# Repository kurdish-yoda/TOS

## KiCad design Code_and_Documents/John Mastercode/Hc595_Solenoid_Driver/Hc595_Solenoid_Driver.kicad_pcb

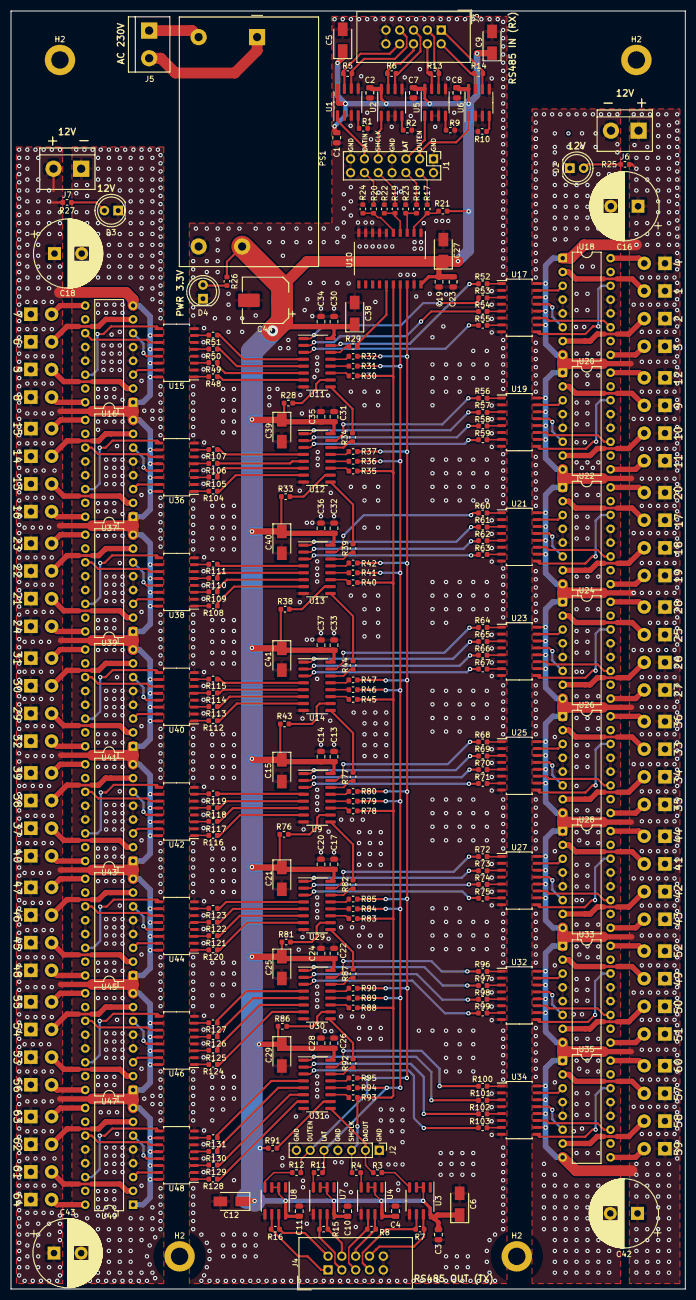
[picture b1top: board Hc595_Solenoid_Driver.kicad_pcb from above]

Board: 2 copper layers, 124.0 x 235.0 mm, 303 parts (0 on the bottom side), 355 nets.

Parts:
C1, C2, C3, C4, C7, C8, C10, C11, C13, C17, C19, C22, C26, C30, C31, C32, C33: 100nF; C_0805_2012Metric_ValInMiddleFABlayer
C5, C6, C9, C12, C15, C21, C25, C27, C29, C38, C39, C40, C41: 4.7uF; D_SMA_SMA_Capacitor
C14, C20, C23, C24, C28, C34, C35, C36, C37: 10nF; C_0805_2012Metric_ValInMiddleFABlayer
C16, C18, C42, C43: 470uF; CP_Radial_D12.5mm_P5.00mm
C44: 470uF; CP_Elec_8x5.4_ModifFABlayer
D2, D3, D4: LD271; LED_D5.0mm_IRGrey
H2, H2#2, H2#3, H2#4: MountingHole_3.2mm_M3_DIN965_Pad_ModifFABlayer
J1: Conn_02x07_Counter_Clockwise; PinHeader_2x07_P2.54mm_Vertical_ModifFABlayer
J2: Conn_01x07; PinHeader_1x07_P2.54mm_Vertical
J3, J4: Conn_02x05_Odd_Even; IDC-Header_2x05_P2.54mm_Vertical_ModifFABlayer
J5, J6, J7: Screw_Terminal_01x02; TerminalBlock_bornier-2_P5.08mm
J8, J9, J10, J11, J12, J13, J14, J15, J16, J17, J18, J19, J20, J21, J22, J23, J24, J25, J26, J27, J28, J29, J30, J31, J32, J33, J34, J35, J36, J37, J38, J39, J40, J41, J42, J43, J44, J45, J46, J47, J48, J49, J50, J51, J52, J53, J54, J55, J56, J57, J58, J59, J60, J61, J62, J63, J64, J65, J66, J67, J68, J69, J70, J71: Conn_01x02; SolderWirePad_1x02_P3.81mm_Drill1.2mm_Diam2.5mm
PS1: IRM-10-3.3; Converter_ACDC_MeanWell_IRM-10-xx_THT
R1, R2, R9, R10: 22k; R_0603_1608Metric_ValInMiddleFABlayer
R3, R4, R11, R12, R17, R18, R19, R20, R29, R30, R31, R32, R34, R35, R36, R37, R39, R40, R41, R42, R44, R45, R46, R47, R77, R78, R79, R80, R82, R83, R84, R85, R87, R88, R89, R90, R92, R93, R94, R95: 33; R_0603_1608Metric_ValInMiddleFABlayer
R5, R6, R7, R8, R13, R14, R15, R16, R26: 120; R_0603_1608Metric_ValInMiddleFABlayer
R21, R22, R23, R24: 33K; R_0603_1608Metric_ValInMiddleFABlayer
R25, R27: 1K; R_0603_1608Metric_ValInMiddleFABlayer
R28, R33, R38, R43, R76, R81, R86, R91: 10k; R_0603_1608Metric_ValInMiddleFABlayer
R48, R49, R50, R51, R52, R53, R54, R55, R56, R57, R58, R59, R60, R61, R62, R63, R64, R65, R66, R67, R68, R69, R70, R71, R72, R73, R74, R75, R96, R97, R98, R99, R100, R101, R102, R103, R104, R105, R106, R107, R108, R109, R110, R111, R112, R113, R114, R115, R116, R117, R118, R119, R120, R121, R122, R123, R124, R125, R126, R127, R128, R129, R130, R131: 200; R_0603_1608Metric_ValInMiddleFABlayer
U1, U2, U3, U4, U5, U6, U7, U8: ST485EBDR; SOIC-8_3.9x4.9mm_P1.27mm_ModifFABlayer
U9, U11, U12, U13, U14, U29, U30, U31: 74HC595; SOIC-16_3.9x9.9mm_P1.27mm
U10: 74HCT541; SO-20_12.8x7.5mm_P1.27mm
U15, U17, U19, U21, U23, U25, U27, U32, U34, U36, U38, U40, U42, U44, U46, U48: TLP291-4; SOIC-16_4.55x10.3mm_P1.27mm
U16, U18, U20, U22, U24, U26, U28, U33, U35, U37, U39, U41, U43, U45, U47, U49: ULN2066B; DIP-16_346_ELL

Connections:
+3V3: C1.1, C2.1, C3.1, C4.1, C5.1, C6.1, C7.1, C8.1, C9.1, C10.1, C11.1, C12.1, C13.1, C14.1, C15.1, C17.1, C19.1, C20.1, C21.1, C22.1, C23.1, C24.1, C25.1, C26.1, C27.1, C28.1, C29.1, C30.1, C31.1, C32.1, C33.1, C34.1, C35.1, C36.1, C37.1, C38.1, C39.1, C40.1, C41.1, C44.1, PS1.4, R21.1, R26.2, R28.1, R33.1, R38.1, R43.1, R76.1, R81.1, R86.1, R91.1, U1.8, U2.8, U3.2, U3.3, U3.8, U4.2, U4.3, U4.8, U5.8, U6.8, U7.2, U7.3, U7.8, U8.2, U8.3, U8.8, U9.16, U10.20, U11.16, U12.16, U13.16, U14.16, U29.16, U30.16, U31.16
+12V_1: C16.1, C42.1, J6.1, J12.1, J13.1, J14.1, J15.1, J16.1, J17.1, J18.1, J19.1, J20.1, J21.1, J22.1, J23.1, J24.1, J25.1, J26.1, J27.1, J28.1, J29.1, J30.1, J31.1, J32.1, J33.1, J34.1, J35.1, J36.1, J37.1, J38.1, J39.1, J40.1, J41.1, J42.1, J43.1, R25.1, U17.10, U17.12, U17.14, U17.16, U18.1, U18.8, U19.10, U19.12, U19.14, U19.16, U20.1, U20.8, U21.10, U21.12, U21.14, U21.16, U22.1, U22.8, U23.10, U23.12, U23.14, U23.16, U24.1, U24.8, U25.10, U25.12, U25.14, U25.16, U26.1, U26.8, U27.10, U27.12, U27.14, U27.16, U28.1, U28.8, U32.10, U32.12, U32.14, U32.16, U33.1, U33.8, U34.10, U34.12, U34.14, U34.16, U35.1, U35.8
+12V_2: C18.1, C43.1, J7.2, J8.1, J9.1, J10.1, J11.1, J44.1, J45.1, J46.1, J47.1, J48.1, J49.1, J50.1, J51.1, J52.1, J53.1, J54.1, J55.1, J56.1, J57.1, J58.1, J59.1, J60.1, J61.1, J62.1, J63.1, J64.1, J65.1, J66.1, J67.1, J68.1, J69.1, J70.1, J71.1, R27.1, U15.10, U15.12, U15.14, U15.16, U16.1, U16.8, U36.10, U36.12, U36.14, U36.16, U37.1, U37.8, U38.10, U38.12, U38.14, U38.16, U39.1, U39.8, U40.10, U40.12, U40.14, U40.16, U41.1, U41.8, U42.10, U42.12, U42.14, U42.16, U43.1, U43.8, U44.10, U44.12, U44.14, U44.16, U45.1, U45.8, U46.10, U46.12, U46.14, U46.16, U47.1, U47.8, U48.10, U48.12, U48.14, U48.16, U49.1, U49.8
DATA_IN: J1.12, R20.2
DATA_IN_BUF: R29.2, U10.15
DATA_IN_RX485: J1.11, U1.1
DATA_IN_RX_A: J3.7, R5.2, U1.6
DATA_IN_RX_B: J3.8, R5.1, U1.7
DATA_OUT: J2.2, R3.2, U31.9
DATA_OUT_TX_A: J4.7, R7.2, U3.6
DATA_OUT_TX_B: J4.8, R7.1, U3.7
GND: C1.2, C2.2, C3.2, C4.2, C5.2, C6.2, C7.2, C8.2, C9.2, C10.2, C11.2, C12.2, C13.2, C14.2, C15.2, C17.2, C19.2, C20.2, C21.2, C22.2, C23.2, C24.2, C25.2, C26.2, C27.2, C28.2, C29.2, C30.2, C31.2, C32.2, C33.2, C34.2, C35.2, C36.2, C37.2, C38.2, C39.2, C40.2, C41.2, C44.2, D4.1, J1.1, J1.2, J1.7, J1.8, J1.13, J1.14, J2.1, J2.4, J2.7, J3.9, J3.10, J4.9, J4.10, PS1.3, R1.2, R2.2, R9.2, R10.2, R22.2, R23.2, R24.2, U1.2, U1.3, U1.5, U2.2, U2.3, U2.5, U3.5, U4.5, U5.2, U5.3, U5.5, U6.2, U6.3, U6.5, U7.5, U8.5, U9.8, U10.1, U10.6, U10.7, U10.8, U10.9, U10.10, U10.19, U11.8, U12.8, U13.8, U14.8, U15.2, U15.4, U15.6, U15.8, U17.2, U17.4, U17.6, U17.8, U19.2, U19.4, U19.6, U19.8, U21.2, U21.4, U21.6, U21.8, U23.2, U23.4, U23.6, U23.8, U25.2, U25.4, U25.6, U25.8, U27.2, U27.4, U27.6, U27.8, U29.8, U30.8, U31.8, U32.2, U32.4, U32.6, U32.8, U34.2, U34.4, U34.6, U34.8, U36.2, U36.4, U36.6, U36.8, U38.2, U38.4, U38.6, U38.8, U40.2, U40.4, U40.6, U40.8, U42.2, U42.4, U42.6, U42.8, U44.2, U44.4, U44.6, U44.8, U46.2, U46.4, U46.6, U46.8, U48.2, U48.4, U48.6, U48.8
GNDPWR1: C16.2, C42.2, D2.1, J6.2, U18.4, U18.5, U18.12, U18.13, U20.4, U20.5, U20.12, U20.13, U22.4, U22.5, U22.12, U22.13, U24.4, U24.5, U24.12, U24.13, U26.4, U26.5, U26.12, U26.13, U28.4, U28.5, U28.12, U28.13, U33.4, U33.5, U33.12, U33.13, U35.4, U35.5, U35.12, U35.13
GNDPWR2: C18.2, C43.2, D3.1, J7.1, U16.4, U16.5, U16.12, U16.13, U37.4, U37.5, U37.12, U37.13, U39.4, U39.5, U39.12, U39.13, U41.4, U41.5, U41.12, U41.13, U43.4, U43.5, U43.12, U43.13, U45.4, U45.5, U45.12, U45.13, U47.4, U47.5, U47.12, U47.13, U49.4, U49.5, U49.12, U49.13
LATCH_CLK: J1.6, R18.2
LATCH_CLK_BUF: J2.5, R11.2, R31.2, R36.2, R41.2, R46.2, R79.2, R84.2, R89.2, R94.2, U10.17
LATCH_CLK_RX485: J1.5, U5.1
LATCH_CLK_RX_A: J3.3, R13.2, U5.6
LATCH_CLK_RX_B: J3.4, R13.1, U5.7
LATCH_CLK_TX_A: J4.3, R15.2, U7.6
LATCH_CLK_TX_B: J4.4, R15.1, U7.7
unnamed: D2.2, R25.2
unnamed: D3.2, R27.2
unnamed: D4.2, R26.1
unnamed: J5.1, PS1.2
unnamed: J5.2, PS1.1
unnamed: J8.2, U16.2
unnamed: J9.2, U16.7
unnamed: J10.2, U16.9
unnamed: J11.2, U16.16
unnamed: J12.2, U18.2
unnamed: J13.2, U18.7
unnamed: J14.2, U18.9
unnamed: J15.2, U18.16
unnamed: J16.2, U20.2
unnamed: J17.2, U20.7
unnamed: J18.2, U20.9
unnamed: J19.2, U20.16
unnamed: J20.2, U22.2
unnamed: J21.2, U22.7
unnamed: J22.2, U22.9
unnamed: J23.2, U22.16
unnamed: J24.2, U24.2
unnamed: J25.2, U24.7
unnamed: J26.2, U24.9
unnamed: J27.2, U24.16
unnamed: J28.2, U26.2
unnamed: J29.2, U26.7
unnamed: J30.2, U26.9
unnamed: J31.2, U26.16
unnamed: J32.2, U28.2
unnamed: J33.2, U28.7
unnamed: J34.2, U28.9
unnamed: J35.2, U28.16
unnamed: J36.2, U33.2
unnamed: J37.2, U33.7
unnamed: J38.2, U33.9
unnamed: J39.2, U33.16
unnamed: J40.2, U35.2
unnamed: J41.2, U35.7
unnamed: J42.2, U35.9
unnamed: J43.2, U35.16
unnamed: J44.2, U37.2
unnamed: J45.2, U37.7
unnamed: J46.2, U37.9
unnamed: J47.2, U37.16
unnamed: J48.2, U39.2
unnamed: J49.2, U39.7
unnamed: J50.2, U39.9
unnamed: J51.2, U39.16
unnamed: J52.2, U41.2
unnamed: J53.2, U41.7
unnamed: J54.2, U41.9
unnamed: J55.2, U41.16
unnamed: J56.2, U43.2
unnamed: J57.2, U43.7
unnamed: J58.2, U43.9
unnamed: J59.2, U43.16
unnamed: J60.2, U45.2
unnamed: J61.2, U45.7
unnamed: J62.2, U45.9
unnamed: J63.2, U45.16
unnamed: J64.2, U47.2
unnamed: J65.2, U47.7
unnamed: J66.2, U47.9
unnamed: J67.2, U47.16
unnamed: J68.2, U49.2
unnamed: J69.2, U49.7
unnamed: J70.2, U49.9
unnamed: J71.2, U49.16
unnamed: R1.1, U1.4
unnamed: R2.1, U2.4
unnamed: R3.1, U3.4
unnamed: R4.1, U4.4
unnamed: R9.1, U5.4
unnamed: R10.1, U6.4
unnamed: R11.1, U7.4
unnamed: R12.1, U8.4
unnamed: R17.1, R21.2, U10.2
unnamed: R18.1, R23.1, U10.3
unnamed: R19.1, R22.1, U10.4
unnamed: R20.1, R24.1, U10.5
unnamed: R28.2, U11.10
unnamed: R29.1, U11.14
unnamed: R30.1, U11.11
unnamed: R31.1, U11.12
unnamed: R32.1, U11.13
unnamed: R33.2, U12.10
unnamed: R34.1, U12.14
unnamed: R35.1, U12.11
unnamed: R36.1, U12.12
unnamed: R37.1, U12.13
unnamed: R38.2, U13.10
unnamed: R39.1, U13.14
unnamed: R40.1, U13.11
unnamed: R41.1, U13.12
unnamed: R42.1, U13.13
unnamed: R43.2, U14.10
unnamed: R44.1, U14.14
unnamed: R45.1, U14.11
unnamed: R46.1, U14.12
unnamed: R47.1, U14.13
unnamed: R48.1, U15.1
unnamed: R49.1, U15.3
unnamed: R50.1, U15.5
unnamed: R51.1, U15.7
unnamed: R52.1, U17.1
unnamed: R53.1, U17.3
unnamed: R54.1, U17.5
unnamed: R55.1, U17.7
unnamed: R56.1, U19.1
unnamed: R57.1, U19.3
unnamed: R58.1, U19.5
unnamed: R59.1, U19.7
unnamed: R60.1, U21.1
unnamed: R61.1, U21.3
unnamed: R62.1, U21.5
unnamed: R63.1, U21.7
unnamed: R64.1, U23.1
unnamed: R65.1, U23.3
unnamed: R66.1, U23.5
unnamed: R67.1, U23.7
unnamed: R68.1, U25.1
unnamed: R69.1, U25.3
unnamed: R70.1, U25.5
unnamed: R71.1, U25.7
unnamed: R72.1, U27.1
unnamed: R73.1, U27.3
unnamed: R74.1, U27.5
unnamed: R75.1, U27.7
unnamed: R76.2, U9.10
unnamed: R77.1, U9.14
unnamed: R78.1, U9.11
unnamed: R79.1, U9.12
unnamed: R80.1, U9.13
unnamed: R81.2, U29.10
unnamed: R82.1, U29.14
unnamed: R83.1, U29.11
unnamed: R84.1, U29.12
unnamed: R85.1, U29.13
unnamed: R86.2, U30.10
unnamed: R87.1, U30.14
unnamed: R88.1, U30.11
unnamed: R89.1, U30.12
unnamed: R90.1, U30.13
unnamed: R91.2, U31.10
unnamed: R92.1, U31.14
unnamed: R93.1, U31.11
unnamed: R94.1, U31.12
unnamed: R95.1, U31.13
unnamed: R96.1, U32.1
unnamed: R97.1, U32.3
unnamed: R98.1, U32.5
unnamed: R99.1, U32.7
unnamed: R100.1, U34.1
unnamed: R101.1, U34.3
unnamed: R102.1, U34.5
unnamed: R103.1, U34.7
unnamed: R104.1, U36.1
unnamed: R105.1, U36.3
unnamed: R106.1, U36.5
unnamed: R107.1, U36.7
unnamed: R108.1, U38.1
unnamed: R109.1, U38.3
unnamed: R110.1, U38.5
unnamed: R111.1, U38.7
unnamed: R112.1, U40.1
unnamed: R113.1, U40.3
unnamed: R114.1, U40.5
unnamed: R115.1, U40.7
unnamed: R116.1, U42.1
unnamed: R117.1, U42.3
unnamed: R118.1, U42.5
unnamed: R119.1, U42.7
unnamed: R120.1, U44.1
unnamed: R121.1, U44.3
unnamed: R122.1, U44.5
unnamed: R123.1, U44.7
unnamed: R124.1, U46.1
unnamed: R125.1, U46.3
unnamed: R126.1, U46.5
unnamed: R127.1, U46.7
unnamed: R128.1, U48.1
unnamed: R129.1, U48.3
unnamed: R130.1, U48.5
unnamed: R131.1, U48.7
unnamed: U15.9, U16.14
unnamed: U15.11, U16.11
unnamed: U15.13, U16.6
unnamed: U15.15, U16.3
unnamed: U17.9, U18.14
unnamed: U17.11, U18.11
unnamed: U17.13, U18.6
unnamed: U17.15, U18.3
unnamed: U19.9, U20.14
unnamed: U19.11, U20.11
unnamed: U19.13, U20.6
unnamed: U19.15, U20.3
unnamed: U21.9, U22.14
unnamed: U21.11, U22.11
unnamed: U21.13, U22.6
unnamed: U21.15, U22.3
unnamed: U23.9, U24.14
unnamed: U23.11, U24.11
unnamed: U23.13, U24.6
unnamed: U23.15, U24.3
unnamed: U25.9, U26.14
unnamed: U25.11, U26.11
unnamed: U25.13, U26.6
unnamed: U25.15, U26.3
unnamed: U27.9, U28.14
unnamed: U27.11, U28.11
unnamed: U27.13, U28.6
unnamed: U27.15, U28.3
unnamed: U32.9, U33.14
unnamed: U32.11, U33.11
unnamed: U32.13, U33.6
unnamed: U32.15, U33.3
unnamed: U34.9, U35.14
unnamed: U34.11, U35.11
unnamed: U34.13, U35.6
unnamed: U34.15, U35.3
unnamed: U36.9, U37.14
unnamed: U36.11, U37.11
unnamed: U36.13, U37.6
unnamed: U36.15, U37.3
unnamed: U38.9, U39.14
unnamed: U38.11, U39.11
unnamed: U38.13, U39.6
unnamed: U38.15, U39.3
unnamed: U40.9, U41.14
unnamed: U40.11, U41.11
unnamed: U40.13, U41.6
unnamed: U40.15, U41.3
unnamed: U42.9, U43.14
unnamed: U42.11, U43.11
unnamed: U42.13, U43.6
unnamed: U42.15, U43.3
unnamed: U44.9, U45.14
unnamed: U44.11, U45.11
unnamed: U44.13, U45.6
unnamed: U44.15, U45.3
unnamed: U46.9, U47.14
unnamed: U46.11, U47.11
unnamed: U46.13, U47.6
unnamed: U46.15, U47.3
unnamed: U48.9, U49.14
unnamed: U48.11, U49.11
unnamed: U48.13, U49.6
unnamed: U48.15, U49.3
OUTPUT_EN: J1.4, R17.2
OUTPUT_EN_BUF: J2.6, R12.2, R32.2, R37.2, R42.2, R47.2, R80.2, R85.2, R90.2, R95.2, U10.18
OUTPUT_EN_RX485: J1.3, U6.1
OUTPUT_EN_RX_A: J3.1, R14.2, U6.6
OUTPUT_EN_RX_B: J3.2, R14.1, U6.7
OUTPUT_EN_TX_A: J4.1, R16.2, U8.6
OUTPUT_EN_TX_B: J4.2, R16.1, U8.7
QA1: R52.2, U11.15
QA2: R56.2, U12.15
QA3: R60.2, U13.15
QA4: R64.2, U14.15
QA5: R68.2, U9.15
QA6: R72.2, U29.15
QA7: R96.2, U30.15
QA8: R100.2, U31.15
QB1: R53.2, U11.1
QB2: R57.2, U12.1
QB3: R61.2, U13.1
QB4: R65.2, U14.1
QB5: R69.2, U9.1
QB6: R73.2, U29.1
QB7: R97.2, U30.1
QB8: R101.2, U31.1
QC1: R54.2, U11.2
QC2: R58.2, U12.2
QC3: R62.2, U13.2
QC4: R66.2, U14.2
QC5: R70.2, U9.2
QC6: R74.2, U29.2
QC7: R98.2, U30.2
QC8: R102.2, U31.2
QD1: R55.2, U11.3
QD2: R59.2, U12.3
QD3: R63.2, U13.3
QD4: R67.2, U14.3
QD5: R71.2, U9.3
QD6: R75.2, U29.3
QD7: R99.2, U30.3
QD8: R103.2, U31.3
QE1: R51.2, U11.4
QE2: R107.2, U12.4
QE3: R111.2, U13.4
QE4: R115.2, U14.4
QE5: R119.2, U9.4
QE6: R123.2, U29.4
QE7: R127.2, U30.4
QE8: R131.2, U31.4
QF1: R50.2, U11.5
QF2: R106.2, U12.5
QF3: R110.2, U13.5
QF4: R114.2, U14.5
QF5: R118.2, U9.5
QF6: R122.2, U29.5
QF7: R126.2, U30.5
QF8: R130.2, U31.5
QG1: R49.2, U11.6
QG2: R105.2, U12.6
QG3: R109.2, U13.6
QG4: R113.2, U14.6
QG5: R117.2, U9.6
QG6: R121.2, U29.6
QG7: R125.2, U30.6
QG8: R129.2, U31.6
QH1: R48.2, U11.7
QH2: R104.2, U12.7
QH3: R108.2, U13.7
QH4: R112.2, U14.7
QH5: R116.2, U9.7
QH6: R120.2, U29.7
QH7: R124.2, U30.7
QH8: R128.2, U31.7
SHIFT_CLK: J1.10, R19.2
SHIFT_CLK_BUF: J2.3, R4.2, R30.2, R35.2, R40.2, R45.2, R78.2, R83.2, R88.2, R93.2, U10.16
SHIFT_CLK_RX485: J1.9, U2.1
SHIFT_CLK_RX_A: J3.5, R6.2, U2.6
SHIFT_CLK_RX_B: J3.6, R6.1, U2.7
SHIFT_CLK_TX_A: J4.5, R8.2, U4.6
SHIFT_CLK_TX_B: J4.6, R8.1, U4.7
SH_REG_1_TO_2: R34.2, U11.9
SH_REG_2_TO_3: R39.2, U12.9
SH_REG_3_TO_4: R44.2, U13.9
SH_REG_4_TO_5: R77.2, U14.9
SH_REG_5_TO_6: R82.2, U9.9
SH_REG_6_TO_7: R87.2, U29.9
SH_REG_7_TO_8: R92.2, U30.9

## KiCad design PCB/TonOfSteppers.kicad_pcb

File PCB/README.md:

# TonsOfSteppers

Stepper Driver Board

## Description
This is an stepper driver board that can drive up to 15 steppers simultaneously,
and up to 8 synchronously. A raspberry is used to control everything. 

## Features
- 8V to 40V input with protection
- 15x stepper pinout.
- Up to 10A capability. 

## Software
All software is written in python. To be used with an RasperryPi with a standart 40pin GPIO.

## Pictures

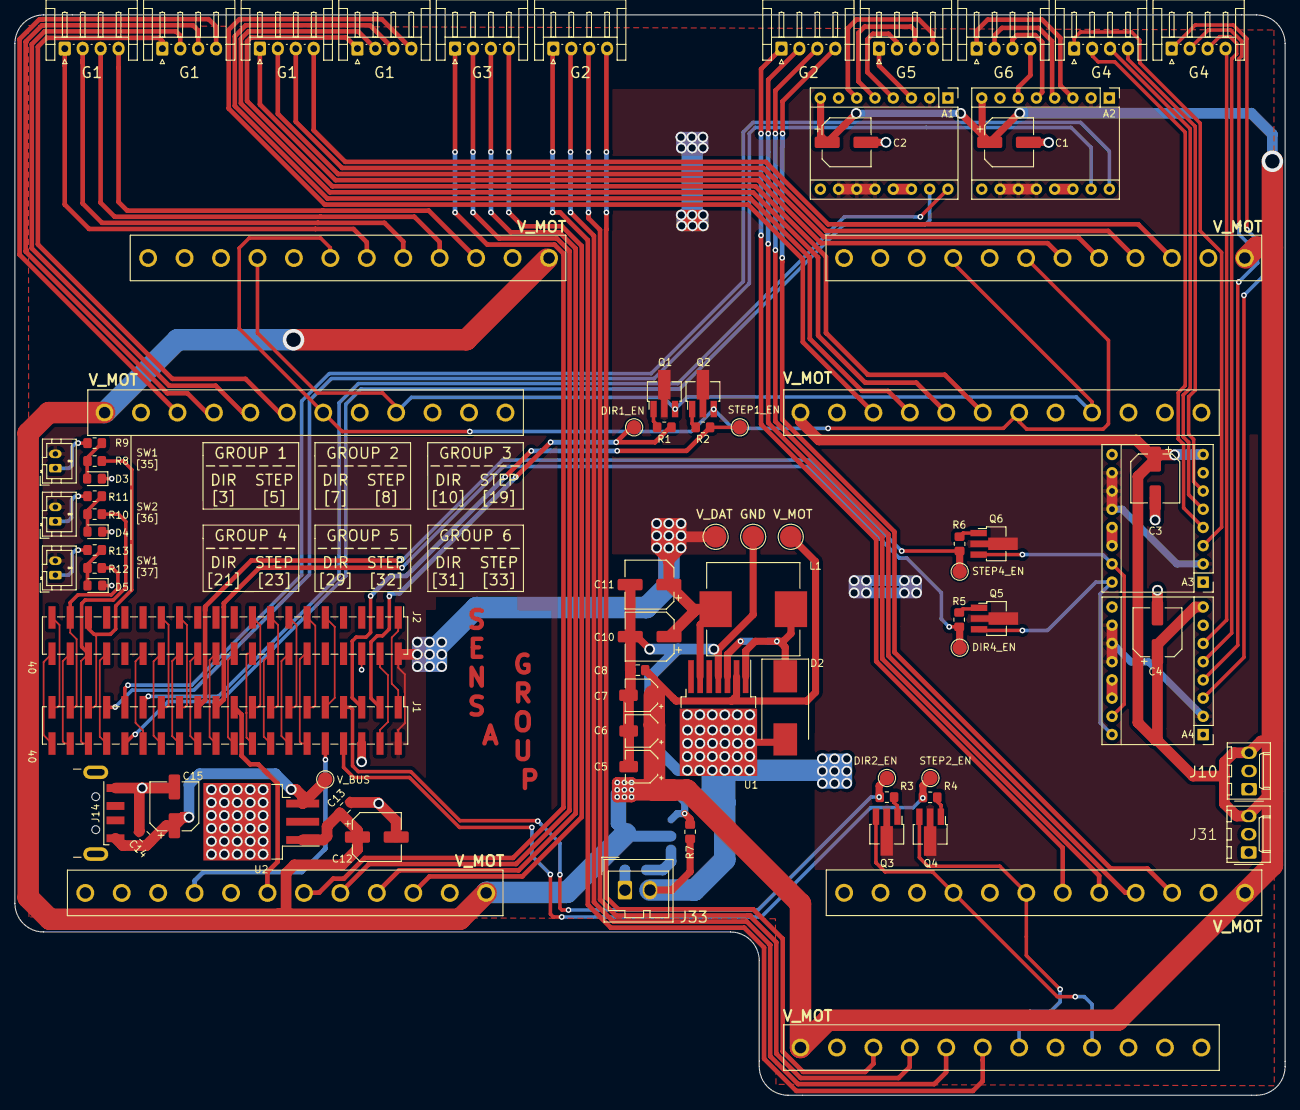
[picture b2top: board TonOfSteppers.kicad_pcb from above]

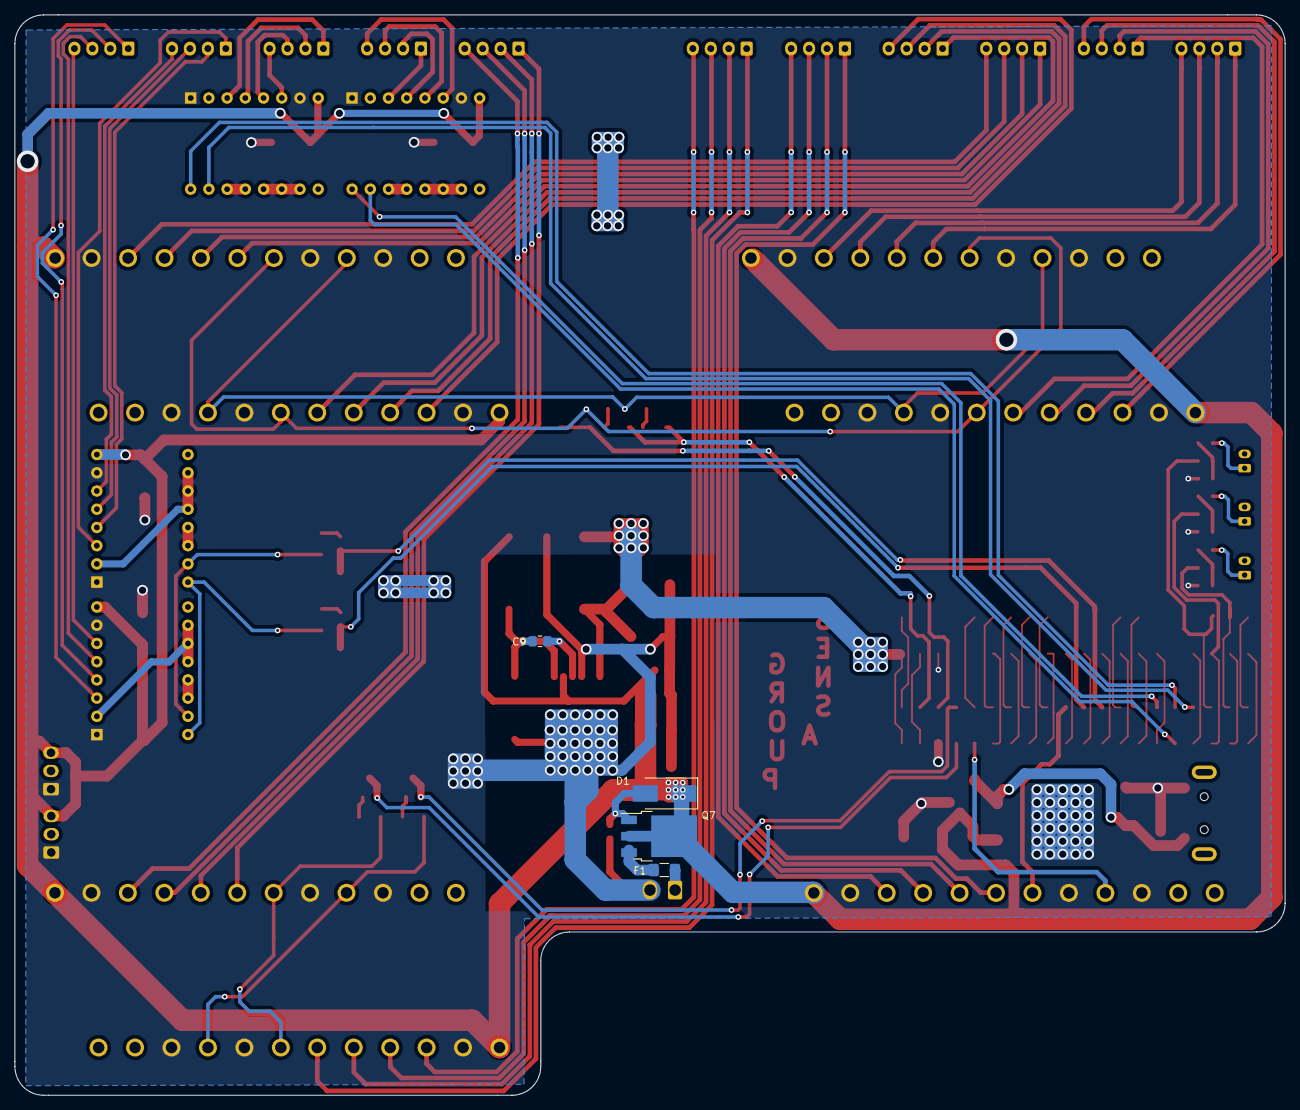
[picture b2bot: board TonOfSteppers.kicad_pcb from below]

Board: 2 copper layers, 177.1 x 150.6 mm, 85 parts (4 on the bottom side), 113 nets.

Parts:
A1, A2, A3, A4: Pololu; Pololu_Breakout-16_15.2x20.3mm
C1, C2, C3, C4, C12, C15: 100uf; CP_Elec_6.3x7.7
C5, C6, C7: 15uf/50V; CP_Elec_4x4.5
C8: 0.47uf; C_0805_2012Metric_Pad1.18x1.45mm_HandSolder
C9, C13, C14: 0.01uf; C_0805_2012Metric_Pad1.18x1.45mm_HandSolder
C10, C11: 180uf/16V; CP_Elec_6.3x7.7
D1: D_Zener_Small; D_SMB_Handsoldering
D2: D_Schottky; D_SMC_Handsoldering
D3, D4, D5: LED; D_0805_2012Metric_Pad1.15x1.40mm_HandSolder
DIR1_EN, DIR2_EN, DIR4_EN: TestPoint_Pad_D2.0mm
F1: Fuse; Fuse_1206_3216Metric_Pad1.42x1.75mm_HandSolder
G3_Con1, G3_Con2, G5_Con1, G5_Con2, G5_Con3, G5_Con4, G5_Con5, G5_Con6, G5_Con7, G5_Con8, G6_Con1: Conn_01x04_Female; JST_EH_S4B-EH_1x04_P2.50mm_Horizontal
GND: TestPoint_Pad_D3.0mm
J1: PI To Board; PinHeader_2x20_P2.54mm_Vertical_SMD
J2: PiGPIO; PinHeader_2x20_P2.54mm_Vertical_SMD
J3, J4, J5, J6, J7, J8, J9: Conn_01x12_Male; Molex_12PIN
J10: FAN_2; Molex_KK-254_AE-6410-03A_1x03_P2.54mm_Vertical
J11, J12, J13: SW; JST_PH_B2B-PH-K_1x02_P2.00mm_Vertical
J14: USB_A; USB_A_CNCTech_1001-011-01101_Horizontal
J31: FAN_1; Molex_KK-254_AE-6410-03A_1x03_P2.54mm_Vertical
J33: V Motor In; Wago_734-132_1x02_P3.50mm_Vertical
L1: 22uH; L_Wuerth_HCI-1365
Q1, Q2, Q3, Q4, Q5, Q6: Q_NPN_BCE; SOT-89-3_Handsoldering
Q7: Q_PMOS_DGS; TO-252-3_TabPin2
R1, R2, R3, R4, R5, R6, R8, R10, R12: 1k; R_0805_2012Metric_Pad1.20x1.40mm_HandSolder
R7, R9, R11, R13: 10k; R_0805_2012Metric_Pad1.20x1.40mm_HandSolder
STEP1_EN, STEP2_EN, STEP4_EN: TestPoint_Pad_D2.0mm
U1: LM2678; TO-263-7_TabPin4
U2: uA7805; TO-263-3_TabPin2
V_BUS: TestPoint_Pad_D2.0mm
V_DAT: TestPoint_Pad_D3.0mm
V_MOT: TestPoint_Pad_D3.0mm

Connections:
1: J1.1, J2.1
4: J1.4, J2.4
9: J1.9, J2.9
11: J1.11, J2.11
12: J1.12, J2.12
13: J1.13, J2.13
14: J1.14, J2.14
15: J1.15, J2.15
16: J1.16, J2.16
17: J1.17, J2.17
18: J1.18, J2.18
20: J1.20, J2.20
22: J1.22, J2.22
24: J1.24, J2.24
25: J1.25, J2.25
26: J1.26, J2.26
27: J1.27, J2.27
28: J1.28, J2.28
30: J1.30, J2.30
34: J1.34, J2.34
35: J1.35, J2.35, R8.2
36: J1.36, J2.36, R10.2
37: J1.37, J2.37, R12.2
38: J1.38, J2.38
39: J1.39, J2.39
40: J1.40, J2.40
/DIR3: J1.10, J9.4
/DIR5: A1.16, J1.29
/DIR6: A2.16, J1.31
/Group 1/DIR1: J3.4, J4.4, J5.4, J6.4, Q1.3
/Group 1/DIR1_EN: DIR1_EN.1, J1.3, R1.1
/Group 1/STEP1: J3.6, J4.6, J5.6, J6.6, Q2.3
/Group 1/STEP1_EN: J1.5, R2.1, STEP1_EN.1
/Group 2/DIR2: J7.4, J8.4, Q3.3
/Group 2/DIR2_EN: DIR2_EN.1, J1.7, R3.1
/Group 2/STEP2: J7.6, J8.6, Q4.3
/Group 2/STEP2_EN: J1.8, R4.1, STEP2_EN.1
/Group 4/DIR4: A3.16, A4.16, Q5.3
/Group 4/DIR4_EN: DIR4_EN.1, J1.21, R5.1
/Group 4/STEP4: A3.15, A4.15, Q6.3
/Group 4/STEP4_EN: J1.23, R6.1, STEP4_EN.1
/Power/V_MOT_MAIN: F1.1, J33.1
/STEP3: J1.19, J9.6
/STEP5: A1.15, J1.32
/STEP6: A2.15, J1.33
GND: A1.1, A1.7, A2.1, A2.7, A3.1, A3.7, A4.1, A4.7, C1.2, C2.2, C3.2, C4.2, C5.2, C6.2, C7.2, C8.2, C10.2, C11.2, C12.2, C13.1, C14.1, C15.2, D2.2, D3.1, D4.1, D5.1, GND.1, J1.6, J2.6, J3.3, J3.5, J3.11, J4.3, J4.5, J4.11, J5.3, J5.5, J5.11, J6.3, J6.5, J6.11, J7.3, J7.5, J7.11, J8.3, J8.5, J8.11, J9.3, J9.5, J9.11, J10.1, J14.4, J31.1, J33.2, R7.2, U1.4, U2.2
unnamed: A1.3, G5_Con1.1
unnamed: A1.4, G5_Con1.2
unnamed: A1.5, G5_Con1.3
unnamed: A1.6, G5_Con1.4
unnamed: A1.13, A1.14
unnamed: A2.3, G6_Con1.1
unnamed: A2.4, G6_Con1.2
unnamed: A2.5, G6_Con1.3
unnamed: A2.6, G6_Con1.4
unnamed: A2.13, A2.14
unnamed: A3.3, G3_Con1.1
unnamed: A3.4, G3_Con1.2
unnamed: A3.5, G3_Con1.3
unnamed: A3.6, G3_Con1.4
unnamed: A3.13, A3.14
unnamed: A4.3, G3_Con2.1
unnamed: A4.4, G3_Con2.2
unnamed: A4.5, G3_Con2.3
unnamed: A4.6, G3_Con2.4
unnamed: A4.13, A4.14
unnamed: C9.1, U1.3
unnamed: C9.2, D2.1, L1.2, U1.1
unnamed: D1.2, Q7.2, R7.1
unnamed: D3.2, R8.1, R9.1
unnamed: D4.2, R10.1, R11.1
unnamed: D5.2, R12.1, R13.1
unnamed: F1.2, Q7.1
unnamed: G5_Con2.1, J3.7
unnamed: G5_Con2.2, J3.8
unnamed: G5_Con2.3, J3.9
unnamed: G5_Con2.4, J3.10
unnamed: G5_Con3.1, J6.7
unnamed: G5_Con3.2, J6.8
unnamed: G5_Con3.3, J6.9
unnamed: G5_Con3.4, J6.10
unnamed: G5_Con4.1, J4.7
unnamed: G5_Con4.2, J4.8
unnamed: G5_Con4.3, J4.9
unnamed: G5_Con4.4, J4.10
unnamed: G5_Con5.1, J5.7
unnamed: G5_Con5.2, J5.8
unnamed: G5_Con5.3, J5.9
unnamed: G5_Con5.4, J5.10
unnamed: G5_Con6.1, J7.7
unnamed: G5_Con6.2, J7.8
unnamed: G5_Con6.3, J7.9
unnamed: G5_Con6.4, J7.10
unnamed: G5_Con7.1, J8.7
unnamed: G5_Con7.2, J8.8
unnamed: G5_Con7.3, J8.9
unnamed: G5_Con7.4, J8.10
unnamed: G5_Con8.1, J9.7
unnamed: G5_Con8.2, J9.8
unnamed: G5_Con8.3, J9.9
unnamed: G5_Con8.4, J9.10
unnamed: J11.1, R9.2
unnamed: J12.1, R11.2
unnamed: J13.1, R13.2
unnamed: Q1.1, R1.2
unnamed: Q2.1, R2.2
unnamed: Q3.1, R3.2
unnamed: Q4.1, R4.2
unnamed: Q5.1, R5.2
unnamed: Q6.1, R6.2
V_BUS: C14.2, C15.1, J14.1, U2.3, V_BUS.1
V_DAT: A1.2, A1.10, A1.11, A1.12, A2.2, A2.10, A2.11, A2.12, A3.2, A3.10, A3.11, A3.12, A4.2, A4.10, A4.11, A4.12, C10.1, C11.1, J1.2, J2.2, J11.2, J12.2, J13.2, L1.1, Q1.2, Q2.2, Q3.2, Q4.2, Q5.2, Q6.2, U1.6, V_DAT.1
V_MOT: A1.8, A2.8, A3.8, A4.8, C1.1, C2.1, C3.1, C4.1, C5.1, C6.1, C7.1, C8.1, C12.1, C13.2, D1.1, J3.12, J4.12, J5.12, J6.12, J7.12, J8.12, J9.12, J10.3, J31.3, Q7.3, U1.2, U2.1, V_MOT.1

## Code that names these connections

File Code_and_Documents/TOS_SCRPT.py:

from time import sleep  #importing delay library
import RPi.GPIO as gpio

gpio.setmode(gpio.BCM)          #Setting GPIO Mode
DIR1 = 2                        # Direction GPIO Pin
STEP1 = 3                       # Step GPIO Pin
gpio.setup(DIR1, gpio.OUT)
gpio.setup(STEP1, gpio.OUT)
DIR2 =  4                        # Direction GPIO Pin
STEP2 =  14                       # Step GPIO Pin
gpio.setup(DIR2, gpio.OUT)
gpio.setup(STEP2, gpio.OUT)
DIR3 =  15                       # Direction GPIO Pin
STEP3 = 10                       # Step GPIO Pin
gpio.setup(DIR3, gpio.OUT)
gpio.setup(STEP3, gpio.OUT)
DIR4 = 9                        # Direction GPIO Pin
STEP4 = 11                       # Step GPIO Pin
gpio.setup(DIR4, gpio.OUT)
gpio.setup(STEP4, gpio.OUT)
DIR5 =  5                       # Direction GPIO Pin
STEP5 = 12                      # Step GPIO Pin
gpio.setup(DIR5, gpio.OUT)
gpio.setup(STEP5, gpio.OUT)
DIR6 =  6                        # Direction GPIO Pin
STEP6 = 13                       # Step GPIO Pin
gpio.setup(DIR6, gpio.OUT)
gpio.setup(STEP6, gpio.OUT)

CW = 1                           # Clockwise Rotation
CCW = 0                          # Counterclockwise Rotation
positions = 3200                 # Steps per revolution, whatever the number is take that number and times it with 16, as the board it set up 16 microstepping (so for nema17, in genneral, 200x16 = 3200
x = 0
y = 0
i = 9
delay = .00103

# move 360 degrees # 
def move360(group, dir):
    # group selection #
    if group == 1:
        x = DIR1
        y = STEP1
    elif group == 2:
        x = DIR2 
        y = STEP2
    elif group == 3:
        x = DIR3
        y = STEP3
    elif group == 4:
        x = DIR4
        y = STEP4
    elif group == 5:
        x = DIR5
        y = STEP5 
    elif group == 6:
        x = DIR6 
        y = STEP6 
    
    # direction statement #
    if dir == CW:
        gpio.output(x, gpio.HIGH)
    elif dir == CCW:
        gpio.output(x, gpio.LOW)
    
    # movement #
    for x in range(0, 3200):
        gpio.output(y, gpio.HIGH)
        sleep(delay)
        gpio.output(y, gpio.LOW)
        sleep(delay)

    return()

#move 180 degress#
def move180(group, dir):
    # group selection #
    if group == 1:
        x = DIR1
        y = STEP1
    elif group == 2:
        x = DIR2 
        y = STEP2
    elif group == 3:
        x = DIR3
        y = STEP3
    elif group == 4:
        x = DIR4
        y = STEP4
    elif group == 5:
        x = DIR5
        y = STEP5 
    elif group == 6:
        x = DIR6 
        y = STEP6 
    
    # direction statement #
    if dir == CW:
        gpio.output(x, gpio.HIGH)
    elif dir == CCW:
        gpio.output(x, gpio.LOW)

    # movement #
    for x in range(0, 1600):
        gpio.output(y, gpio.HIGH)
        sleep(delay)
        gpio.output(y, gpio.LOW)
        sleep(delay)
        
    return()

#move 90 degress#
def move90(group, dir):
    # group selection #
    if group == 1:
        x = 13
        y = 12
    elif group == 2:
        x = DIR2
        y = STEP2
    elif group == 3:
        x = DIR3
        y = STEP3
    elif group == 4:
        x = DIR4
        y = STEP4
    elif group == 5:
        x = DIR5
        y = STEP5
    elif group == 6:
        x = DIR6
        y = STEP6
    
    # direction statement #
    if dir == CW:
        gpio.output(x, gpio.HIGH)
    elif dir == CCW:
        gpio.output(x, gpio.LOW)

    # movement #
    for z in range(0, 800):
        gpio.output(y, gpio.HIGH)
        sleep(delay)
        gpio.output(y, gpio.LOW)
        sleep(delay)
        
    return()

#move 45 degress@
def move45(group, dir):
    # group selection #
    if group == 1:
        x = DIR1
        y = STEP1
    elif group == 2:
        x = DIR2 
        y = STEP2
    elif group == 3:
        x = DIR3
        y = STEP3
    elif group == 4:
        x = DIR4
        y = STEP4
    elif group == 5:
        x = DIR5
        y = STEP5 
    elif group == 6:
        x = DIR6 
        y = STEP6 
    
    # direction statement #
    if dir == CW:
        gpio.output(x, gpio.HIGH)
    elif dir == CCW:
        gpio.output(x, gpio.LOW)

    # movement #
    for x in range(0, 400):
        gpio.output(y, gpio.HIGH)
        sleep(delay)
        gpio.output(y, gpio.LOW)
        sleep(delay)
        
    return()


#move a defined number of degress
def move(group, dir, degree):
    degree = degree * i
    # group selection #
    if group == 1:
        x = DIR1
        y = STEP1
    elif group == 2:
        x = DIR2 
        y = STEP2
    elif group == 3:
        x = DIR3
        y = STEP3
    elif group == 4:
        x = DIR4
        y = STEP4
    elif group == 5:
        x = DIR5
        y = STEP5 
    elif group == 6:
        x = DIR6 
        y = STEP6 

    # direction statement #
    if dir == CW:
        gpio.output(x, gpio.HIGH)
    elif dir == CCW:
        gpio.output(x, gpio.LOW)

    # movement #
    for x in range(0, degree):
        gpio.output(y, gpio.HIGH)
        sleep(delay)
        gpio.output(y, gpio.LOW)
        sleep(delay)
        
    return()

#START
print("Starting Program")

move(1, CW, 90)
move(6, CW, 90)
move(5, CW, 90)
move(4, CW, 90)
print("********************")
print("Finishing Program")

gpio.cleanup()

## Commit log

2021-01-20 Master commit
    Master commit
2021-01-20 upgrade
2021-04-03 TOS new version
    -Added usb power for display.
2021-07-25 Sticker Images
2021-08-02 Testing
2021-08-08 Deleted footprint
2021-12-25 Master code
    Added solenoid functionality utilizing a daughter board.
